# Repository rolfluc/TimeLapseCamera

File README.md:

# TimeLapseCamera
Repo Housing the Mechanical, Electrical, Tests, and Software / layer config for taking an RPI Zero 2W into a time lapse / mobile camera for a rechargable battery.
The following steps are to setup yocto for building an RPI image for the RPI Zero W2
```
git clone -b scarthgap https://git.yoctoproject.org/poky
```
```
git clone -b scarthgap https://git.yoctoproject.org/meta-raspberrypi
```
```
source poky/oe-init-build-env build-rpi
```
```
bitbake-layers add-layer ../meta-raspberrypi
```
-> Confirm layer was added to conf/bblayers.conf

```
set local.conf -> 'MACHINE ??=' -> 'MACHINE = "raspberrypi0-2w-64"' 
```
^-- this matches ~/yocto-rpi/meta-raspberrypi/conf/machine/
```
set local.conf -> IMAGE_FSTYPES = "wic.bz2"
set local.conf -> LICENSE_FLAGS_ACCEPTED = "synaptics-killswitch"
```
```
cd ~/yocto-rpi/build-rpi
```
```
bitbake core-image-base
```

Once Complete, check in : ~/yocto-rpi/build-rpi/tmp/deploy/images/raspberrypi0-2w-64/
for a file:
core-image-base-raspberrypi0-2w-64.rootfs.wic.bz2

In this case, WSL is being used to build, so RPI Imager is used to flash to an SD card.

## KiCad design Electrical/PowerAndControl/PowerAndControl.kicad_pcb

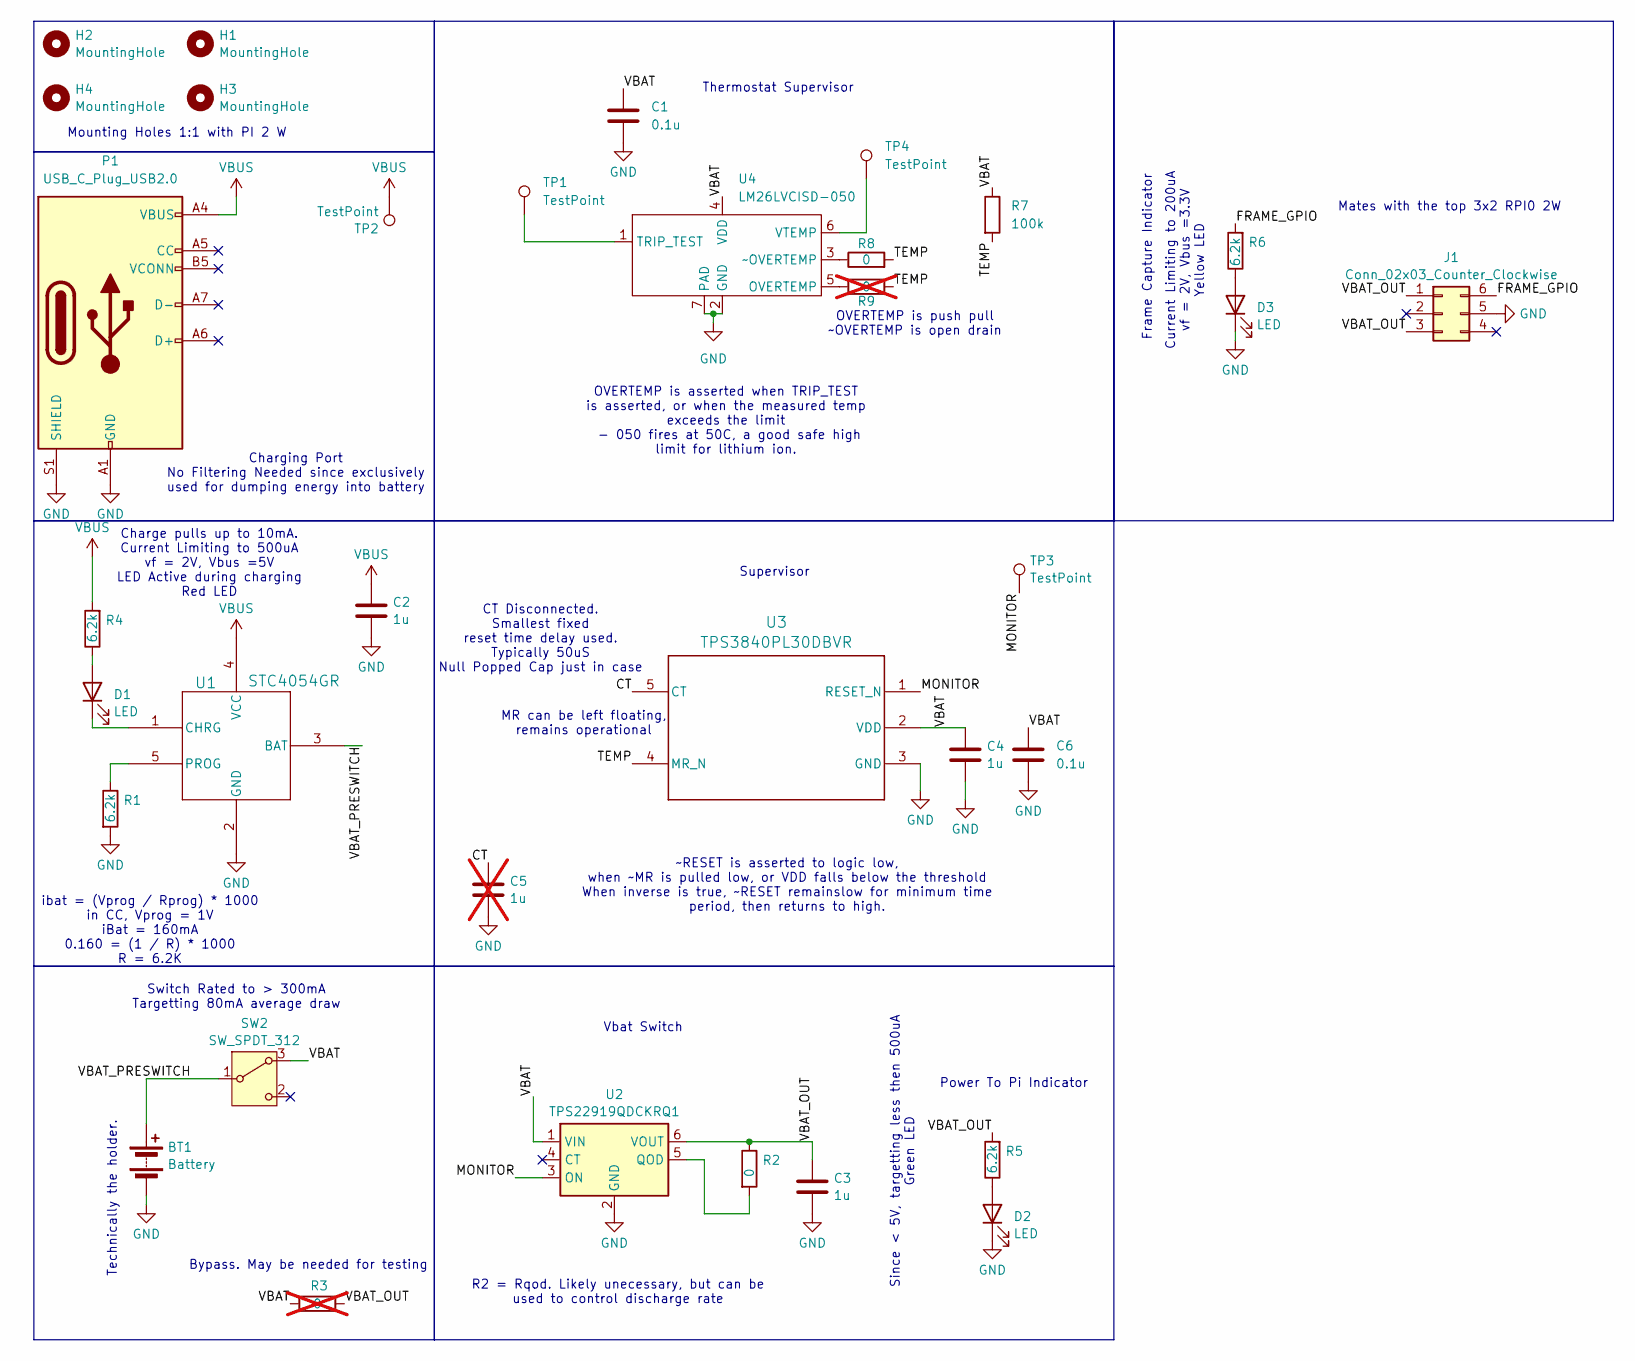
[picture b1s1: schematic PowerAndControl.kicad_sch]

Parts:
BT1: Battery; BAT_BK-53; MPN BAT_BK-53
C1, C6: 0.1u; C_0402_1005Metric_Pad0.74x0.62mm_HandSolder
C2, C3, C4: 1u; C_0402_1005Metric_Pad0.74x0.62mm_HandSolder; MPN CL05A105KO5NNNC
C5: 1u; C_0603_1608Metric_Pad1.08x0.95mm_HandSolder; not fitted
D1: LED; LED_0604; MPN LTST-S271KRKT
D2: LED; LED_0604; MPN LTST-S271KGKT
D3: LED; LED_0604; MPN LTST-S271KSKT
H1, H2, H3, H4: MountingHole; MountingHole_2.7mm_M2.5
J1: Conn_02x03_Counter_Clockwise; PinHeader_2x03_P2.54mm_Vertical
P1: USB_C_Plug_USB2.0; USB_C_Receptacle_GCT_USB4085
R1, R4, R5, R6: 6.2k; R_0402_1005Metric_Pad0.72x0.64mm_HandSolder
R2, R8: 0; R_0402_1005Metric_Pad0.72x0.64mm_HandSolder
R3: 0; R_0603_1608Metric_Pad0.98x0.95mm_HandSolder; not fitted
R7: 100k; R_0402_1005Metric_Pad0.72x0.64mm_HandSolder
R9: 0; R_0402_1005Metric_Pad0.72x0.64mm_HandSolder; not fitted
SW2: SW_SPDT_312; EGJ1210; MPN EGJ1210
TP1, TP2, TP3, TP4: TestPoint; TestPoint_Pad_1.0x1.0mm
U1: STC4054GR; TSOT-23-5_HandSoldering
U2: TPS22919QDCKRQ1; SOT-363_SC-70-6
U3: TPS3840PL30DBVR; SC-74A-5_1.55x2.9mm_P0.95mm
U4: LM26LVCISD-050; WSON-6-1EP_2x2mm_P0.65mm_EP1x1.6mm_ThermalVias

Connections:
/CT: C5.1, U3.5 (CT)
/FRAME_GPIO: J1.6, R6.2
/MONITOR: TP3.1, U2.3 (ON), U3.1 (RESET_N)
/TEMP: R7.2, R8.2, R9.2, U3.4 (MR_N)
/VBAT: C1.1, C4.1, C6.1, R3.1, R7.1, SW2.3 (A), U2.1 (VIN), U3.2 (VDD), U4.4 (VDD)
/VBAT_OUT: C3.1, J1.1, J1.3, R2.1, R3.2, R5.2, U2.6 (VOUT)
/VBAT_PRESWITCH: BT1.1 (+), SW2.1 (B), U1.3 (BAT)
GND: BT1.2 (-), C1.2, C2.2, C3.2, C4.2, C5.2, C6.2, D2.1 (K), D3.1 (K), J1.5, P1.A1 (GND), P1.A12 (GND), P1.B1 (GND), P1.B12 (GND), P1.S1 (SHIELD), R1.2, U1.2 (GND), U2.2 (GND), U3.3 (GND), U4.2 (GND), U4.7 (PAD)
unnamed: D1.2 (A), R4.1
unnamed: D1.1 (K), U1.1 (CHRG)
unnamed: D2.2 (A), R5.1
unnamed: D3.2 (A), R6.1
unnamed: R1.1, U1.5 (PROG)
unnamed: R2.2, U2.5 (QOD)
unnamed: R9.1, U4.5 (OVERTEMP)
unnamed: TP1.1, U4.1 (TRIP_TEST)
unnamed: TP4.1, U4.6 (VTEMP)
unnamed: R8.1, U4.3 (~OVERTEMP)
VBUS: C2.1, P1.A4 (VBUS), P1.A9 (VBUS), P1.B4 (VBUS), P1.B9 (VBUS), R4.2, TP2.1, U1.4 (VCC)

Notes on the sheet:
Technically the holder.
OVERTEMP is push pull ~OVERTEMP is open drain
Mounting Holes 1:1 with PI 2 W
Thermostat Supervisor
OVERTEMP is asserted when TRIP_TEST is asserted, or when the measured temp exceeds the limit - 050 fires at 50C, a good safe high limit for lithium ion.
Supervisor
Mates with the top 3x2 RPI0 2W
Power To Pi Indicator
CT Disconnected. Smallest fixed reset time delay used. Typically 50uS Null Popped Cap just in case
MR can be left floating, remains operational
~RESET is asserted to logic low, when ~MR is pulled low, or VDD falls below the threshold When inverse is true, ~RESET remainslow for minimum time period, then returns to high.
Charge pulls up to 10mA. Current Limiting to 500uA vf = 2V, Vbus =5V LED Active during charging Red LED
Switch Rated to > 300mA Targetting 80mA average draw
R2 = Rqod. Likely unecessary, but can be used to control discharge rate
ibat = (Vprog / Rprog) * 1000 in CC, Vprog = 1V iBat = 160mA 0.160 = (1 / R) * 1000 R = 6.2K
Current Limiting to 200uA vf = 2V, Vbus =3.3V Yellow LED
Bypass. May be needed for testing
Vbat Switch
Since < 5V, targetting less then 500uA Green LED
Frame Capture Indicator
Charging Port No Filtering Needed since exclusively used for dumping energy into battery

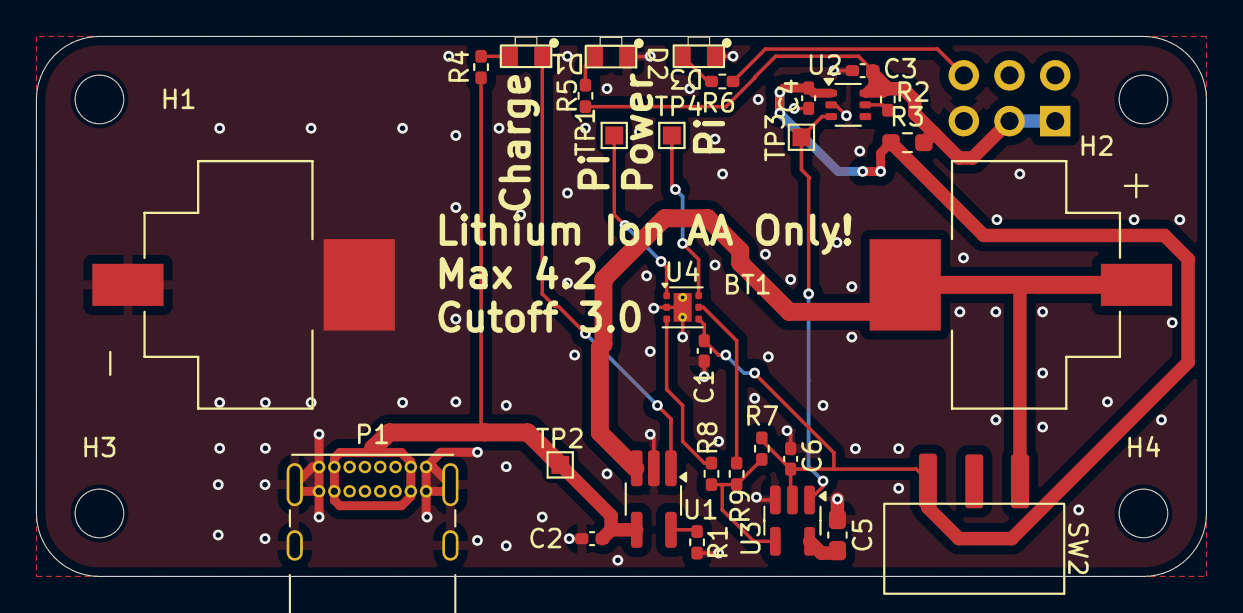
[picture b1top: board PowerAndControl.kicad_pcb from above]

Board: 2 copper layers, 65.0 x 30.0 mm, 34 parts (1 on the bottom side), 19 nets.

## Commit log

2026-06-09 First commit, adding basics, and build for yocto script
2026-06-09 Missed .wic files
2026-06-09 Expanding Build Script
2026-06-09 Working Build Script / Local Conf
2026-06-09 Starting Mechanical
2026-06-09 Adding first custom image
2026-06-10 Added Boot Logs
2026-06-10 First pass Electrical
    Has Schematic.
    Has Outline,
2026-06-10 Layout of AA variant complete. Need to check pinout 2x more
2026-06-11 Cleaner Schematic / LED Indicators, better Layout
    Added 3 LEDs for indicators.
    Shcematic Cleaned up in general.
    New Charger component
2026-06-12 WIP Layout
2026-06-12 Cleared a TODO
2026-06-12 Rough Positioning of Camera Module, with Cable.
2026-06-12 Added additional Silkscreen
2026-06-15 WIP - added additionalCutouts
2026-06-15 Rerouted Switch, Added Thermostat
    Switch is now on the same side as the USB port. Should help
    reduce z axis stackup.
    Added thermostat, will shutoff if high temp
2026-06-16 Fixed up / Repositioned Model
2026-06-16 Fixed Minor Issue. Getting Fabbed
2026-06-17 First Pass Housing
2026-06-18 Starting some Integration, current down to 100mA
2026-06-18 Removing otg, audio
2026-06-18 Attempting to add Bluetooth
2026-06-22 WIP Adding RPI variant. For grins.
